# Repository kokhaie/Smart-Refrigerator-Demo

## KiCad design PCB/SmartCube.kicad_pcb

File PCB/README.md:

# PCB Bill of Materials

The KiCad-generated BOM is mirrored into the documentation site under `docs/` so it can be published through GitHub Pages.

- **Live BOM:** https://kokhaie.github.io/Smart-Refrigerator-Demo/bom.html

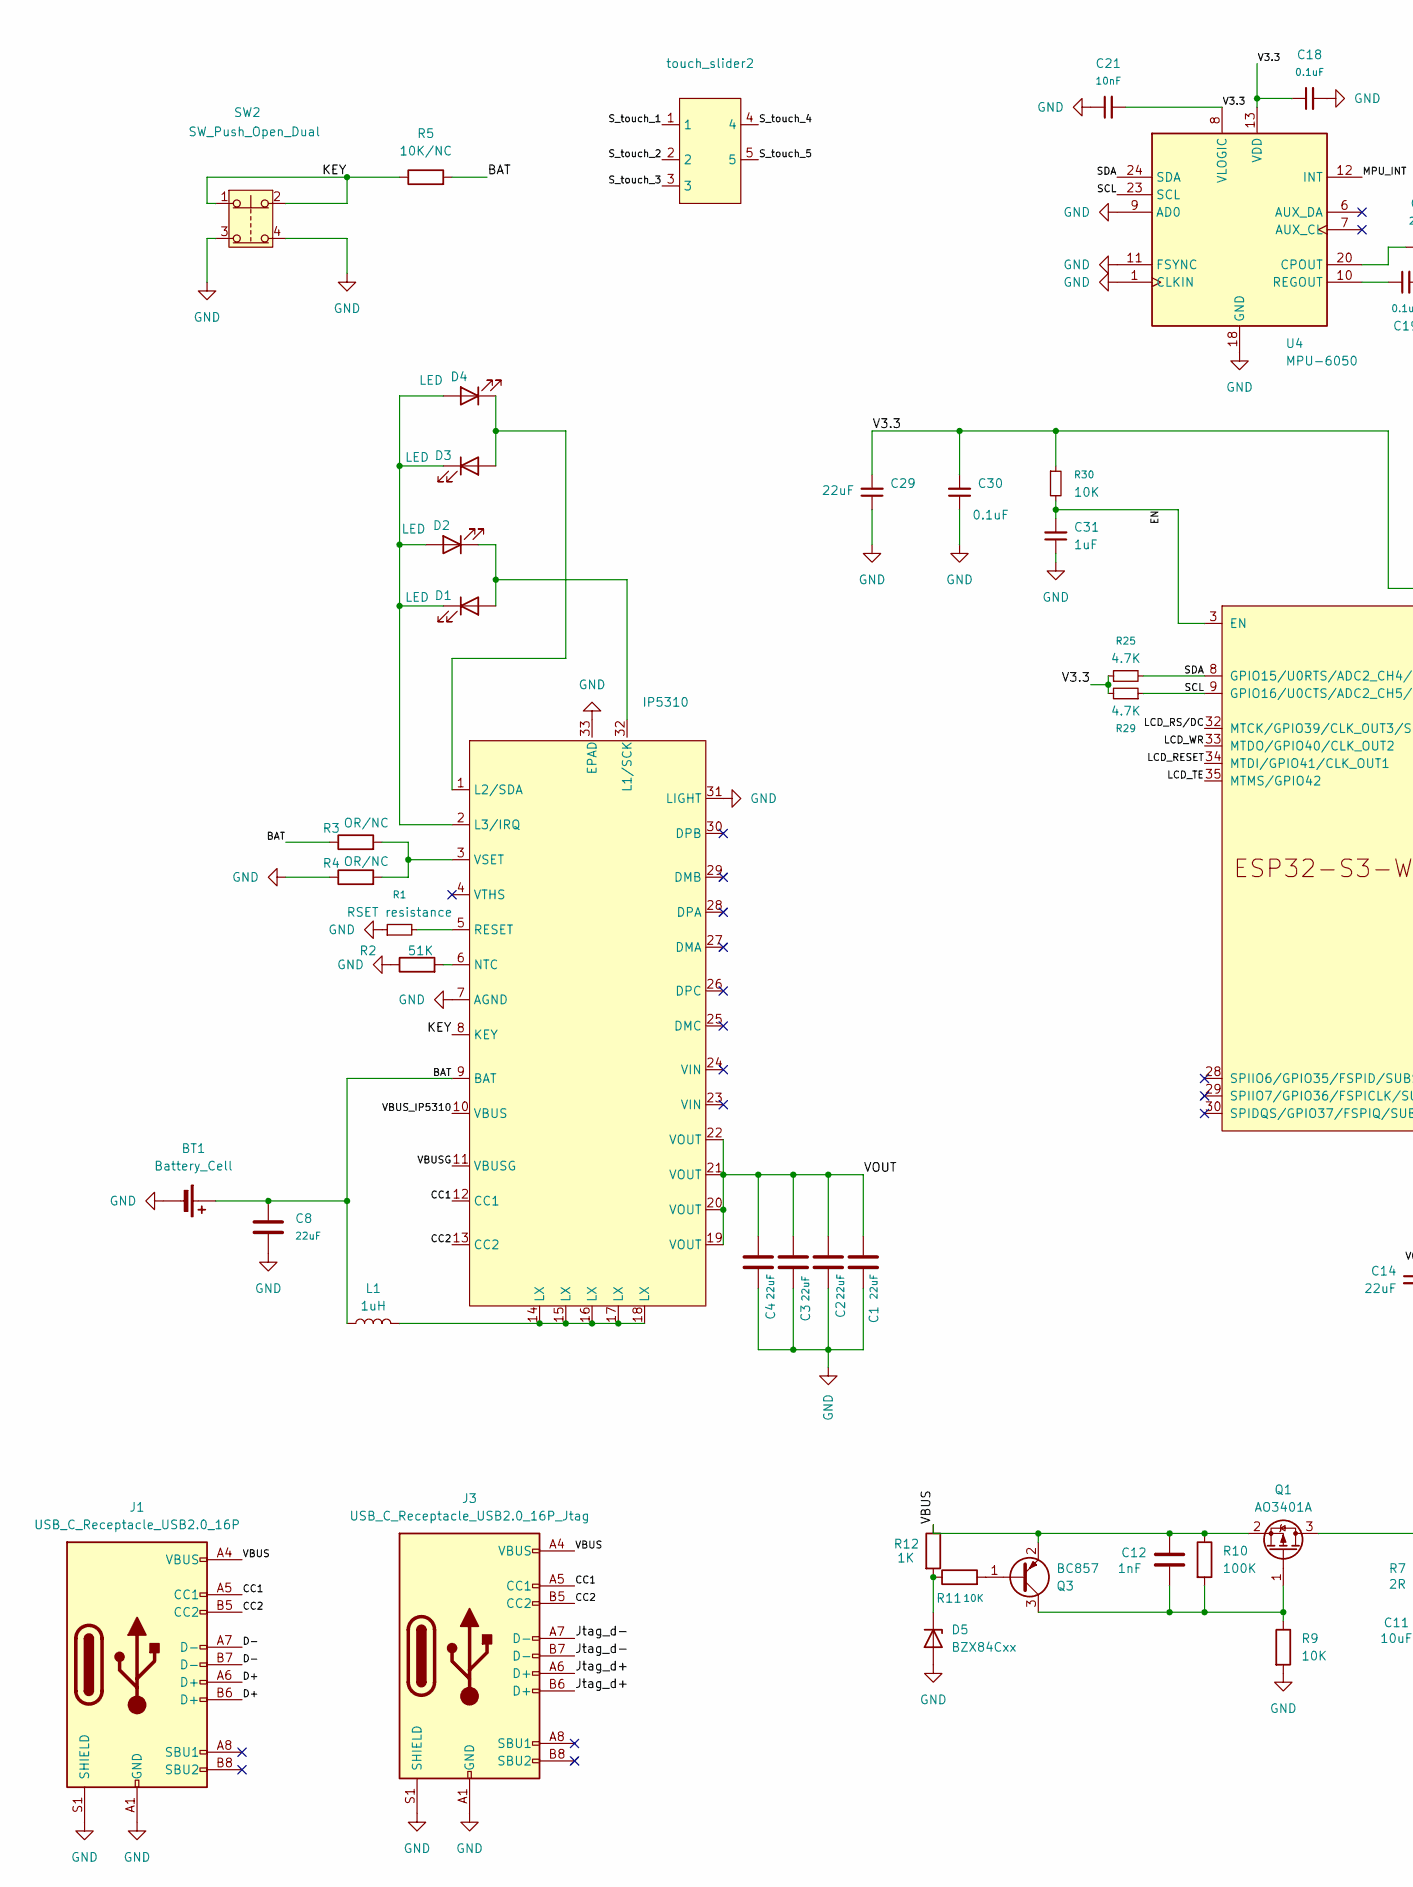
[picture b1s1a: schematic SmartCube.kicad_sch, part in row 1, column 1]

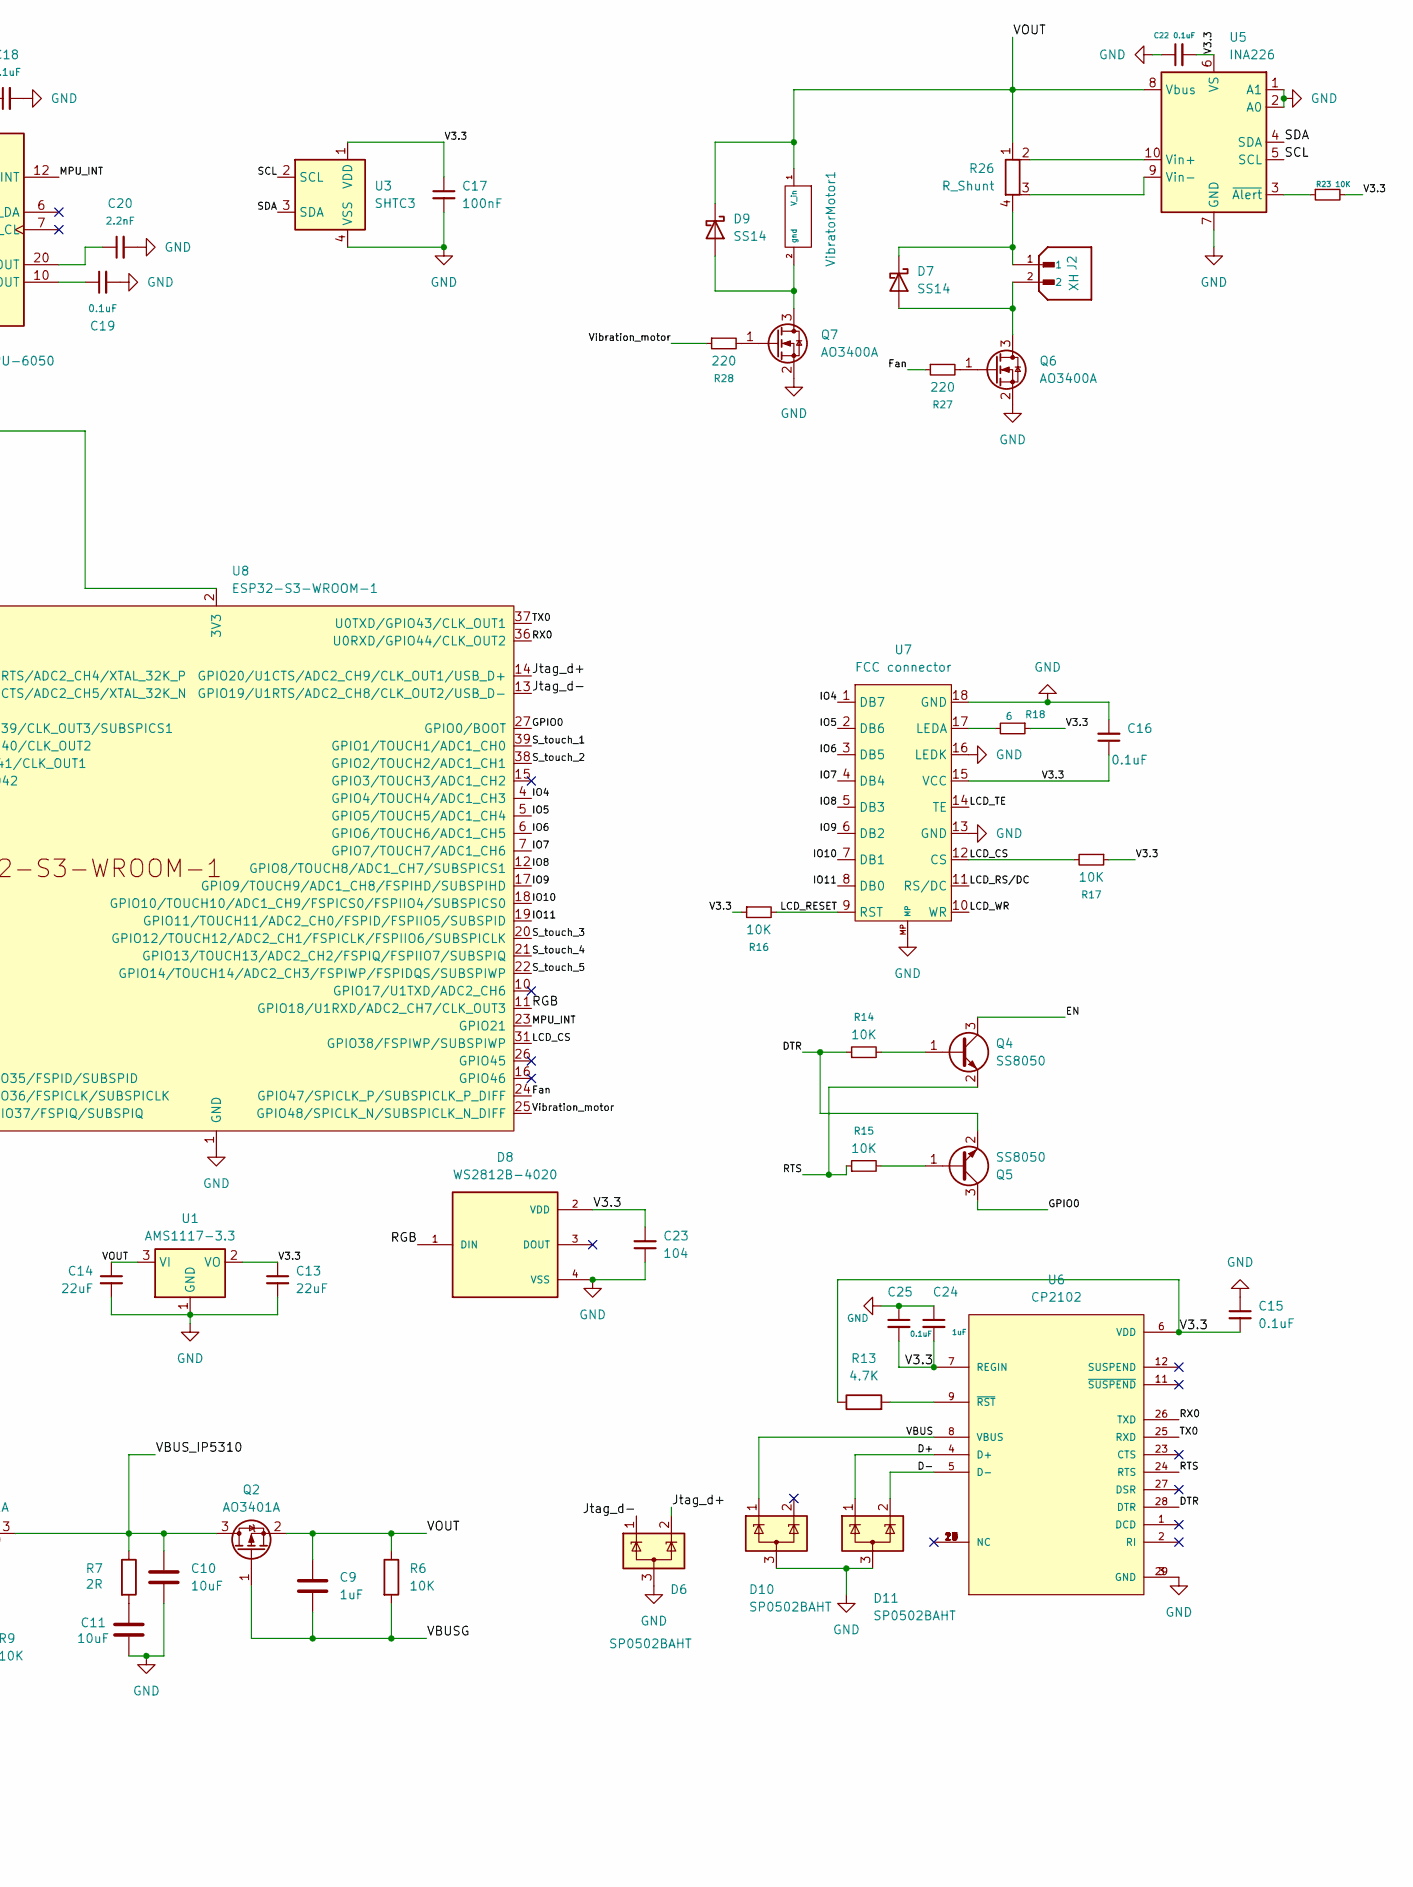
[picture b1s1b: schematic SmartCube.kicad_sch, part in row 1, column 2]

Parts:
BT1: Battery_Cell; vibrator connector
C1, C2, C3, C4, C8, C13, C14: 22uF; C_0805_2012Metric
C9, C24, C31: 1uF; C_0805_2012Metric
C10, C11: 10uF; C_0805_2012Metric
C12: 1nF; C_0805_2012Metric
C15, C16, C18, C19, C22, C25, C30: 0.1uF; C_0805_2012Metric
C17: 100nF; C_0805_2012Metric
C20: 2.2nF; C_0805_2012Metric
C21: 10nF; C_0805_2012Metric
C23: 104; C_0805_2012Metric
C29: 22uF; CP_EIA-3528-21_Kemet-B
D1, D2, D3, D4: LED; LED_0603_1608Metric
D5: BZX84Cxx; SOT-23
D6, D10, D11: SP0502BAHT; SOT-23
D7, D9: SS14; D_SMA
D8: WS2812B-4020; LED_WS2812B-4020; PARTREV V1.2
IP5310: IP5310
J1: USB_C_Receptacle_USB2.0_16P; USB_C_Receptacle_GCT_USB4105-xx-A_16P_TopMnt_Horizontal
J2: XH; vibrator connector; PARTREV N/A
J3: USB_C_Receptacle_USB2.0_16P_Jtag; USB_C_Receptacle_GCT_USB4105-xx-A_16P_TopMnt_Horizontal
L1: 1uH; L_7.3x7.3_H4.5
Q1, Q2: AO3401A; SOT-23
Q3: BC857; SOT-23
Q4, Q5: SS8050; SOT-23
Q6, Q7: AO3400A; SOT-23
R1: RSET resistance; R_0805_2012Metric
R2: 51K; R_0603_1608Metric
R3, R4: OR/NC; R_0805_2012Metric
R5: 10K/NC; R_0805_2012Metric
R6, R9, R11, R14, R15, R16, R17, R23, R30: 10K; R_0805_2012Metric
R7: 2R; R_0805_2012Metric
R10: 100K; R_0805_2012Metric
R12: 1K; R_0805_2012Metric
R13, R25, R29: 4.7K; R_0805_2012Metric
R18: 6; R_0805_2012Metric
R26: R_Shunt; R_Shunt_Vishay_WSK2512_6332Metric_T1.19mm
R27, R28: 220; R_0805_2012Metric
SW2: SW_Push_Open_Dual; 1189UE
U1: AMS1117-3.3; SOT-223-3_TabPin2
U3: SHTC3; Sensirion_DFN-4-1EP_2x2mm_P1mm_EP0.7x1.6mm
U4: MPU-6050; InvenSense_QFN-24_4x4mm_P0.5mm
U5: INA226; VSSOP-10_3x3mm_P0.5mm
U6: CP2102; QFN50P500X500X100-29N
U7: FCC connector; Untitled
U8: ESP32-S3-WROOM-1
VibratorMotor1: vibrator connector
touch_slider2: TouchSlider-5_50x10mm

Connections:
/BAT: BT1.1 (+), C8.1, IP5310.9 (BAT), L1.1, R3.1, R5.2
/CC1: IP5310.12 (CC1), J1.A5 (CC1), J3.A5 (CC1)
/CC2: IP5310.13 (CC2), J1.B5 (CC2), J3.B5 (CC2)
/D+: D11.1 (K), J1.A6 (D+), J1.B6 (D+), U6.4 (D+)
/D-: D11.2 (K), J1.A7 (D-), J1.B7 (D-), U6.5 (D-)
/DTR: Q5.2 (E), R14.1, U6.28 (DTR)
/EN: C31.2, Q4.3 (C), R30.2, U8.3 (EN)
/Fan: R27.1, U8.24 (GPIO47/SPICLK_P/SUBSPICLK_P_DIFF)
/GPIO0: Q5.3 (C), U8.27 (GPIO0/BOOT)
/IO4: U7.1 (DB7), U8.4 (GPIO4/TOUCH4/ADC1_CH3)
/IO5: U7.2 (DB6), U8.5 (GPIO5/TOUCH5/ADC1_CH4)
/IO6: U7.3 (DB5), U8.6 (GPIO6/TOUCH6/ADC1_CH5)
/IO7: U7.4 (DB4), U8.7 (GPIO7/TOUCH7/ADC1_CH6)
/IO8: U7.5 (DB3), U8.12 (GPIO8/TOUCH8/ADC1_CH7/SUBSPICS1)
/IO9: U7.6 (DB2), U8.17 (GPIO9/TOUCH9/ADC1_CH8/FSPIHD/SUBSPIHD)
/IO10: U7.7 (DB1), U8.18 (GPIO10/TOUCH10/ADC1_CH9/FSPICS0/FSPIIO4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)
/IO11: U7.8 (DB0), U8.19 (GPIO11/TOUCH11/ADC2_CH0/FSPID/FSPIIO5/S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)
/Jtag_d+: D6.2 (K), J3.A6 (D+), J3.B6 (D+), U8.14 (GPIO20/U1CTS/ADC2_CH9/CLK_OUT1/USB_D+)
/Jtag_d-: D6.1 (K), J3.A7 (D-), J3.B7 (D-), U8.13 (GPIO19/U1RTS/ADC2_CH8/CLK_OUT2/USB_D-)
/KEY: IP5310.8 (KEY), R5.1, SW2.1, SW2.2
/LCD_CS: R17.2, U7.12 (CS), U8.31 (GPIO38/FSPIWP/SUBSPIWP)
/LCD_RESET: R16.2, U7.9 (RST), U8.34 (MTDI/GPIO41/CLK_OUT1)
/LCD_RS/DC: U7.11 (RS/DC), U8.32 (MTCK/GPIO39/CLK_OUT3/SUBSPICS1)
/LCD_TE: U7.14 (TE), U8.35 (MTMS/GPIO42)
/LCD_WR: U7.10 (WR), U8.33 (MTDO/GPIO40/CLK_OUT2)
/MPU_INT: U4.12 (INT), U8.23 (GPIO21)
/RGB: D8.1 (DIN), U8.11 (GPIO18/U1RXD/ADC2_CH7/CLK_OUT3); also elsewhere on the board
/RTS: Q4.2 (E), R15.1, U6.24 (RTS)
/RX0: U6.26 (TXD), U8.36 (U0RXD/GPIO44/CLK_OUT2)
/SCL: R29.1, U3.2 (SCL), U4.23 (SCL), U5.5 (SCL), U8.9 (GPIO16/U0CTS/ADC2_CH5/XTAL_32K_N)
/SDA: R25.2, U3.3 (SDA), U4.24 (SDA), U5.4 (SDA), U8.8 (GPIO15/U0RTS/ADC2_CH4/XTAL_32K_P)
/S_touch_1: U8.39 (GPIO1/TOUCH1/ADC1_CH0), touch_slider2.1
/S_touch_2: U8.38 (GPIO2/TOUCH2/ADC1_CH1), touch_slider2.2
/S_touch_3: U8.20 (GPIO12/TOUCH12/ADC2_CH1/FSPICLK/FSPIIO6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), touch_slider2.3
/S_touch_4: U8.21 (GPIO13/TOUCH13/ADC2_CH2/FSPIQ/FSPIIO7/S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), touch_slider2.4
/S_touch_5: U8.22 (GPIO14/TOUCH14/ADC2_CH3/FSPIWP/FSPIDQS/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), touch_slider2.5
/TX0: U6.25 (RXD), U8.37 (U0TXD/GPIO43/CLK_OUT1)
/V3.3: C13.1, C15.2, C16.1, C17.1, C18.1, C21.2, C22.2, C23.2, C24.2, C25.2, C29.2, C30.2, D8.2 (VDD), R13.1, R16.1, R17.1, R18.1, R23.2, R25.1, R29.2, R30.1, U1.2 (VO), U3.1 (VDD), U4.8 (VLOGIC), U4.13 (VDD), U5.6 (VS), U6.6 (VDD), U6.7 (REGIN), U7.15 (VCC), U8.2 (3V3); also elsewhere on the board
/VBUS: C12.1, D10.1 (K), J1.A4 (VBUS), J1.A9 (VBUS), J1.B4 (VBUS), J1.B9 (VBUS), J3.A4 (VBUS), J3.A9 (VBUS), J3.B4 (VBUS), J3.B9 (VBUS), Q1.2 (S), Q3.2 (E), R10.1, R12.1, U6.8 (VBUS)
/VBUSG: C9.2, IP5310.11 (VBUSG), Q2.1 (G), R6.2
/VBUS_IP5310: C10.1, IP5310.10 (VBUS), Q1.3 (D), Q2.3 (D), R7.1
/VOUT: C1.1, C2.1, C3.1, C4.1, C9.1, C14.1, D9.1 (K), IP5310.19 (VOUT), IP5310.20 (VOUT), IP5310.21 (VOUT), IP5310.22 (VOUT), Q2.2 (S), R6.1, R26.1, U1.3 (VI), U5.8 (Vbus), VibratorMotor1.1 (V_in)
/Vibration_motor: R28.1, U8.25 (GPIO48/SPICLK_N/SUBSPICLK_N_DIFF)
GND: BT1.2 (-), C1.2, C2.2, C3.2, C4.2, C8.2, C10.2, C11.2, C13.2, C14.2, C15.1, C16.2, C17.2, C18.2, C19.2, C20.2, C21.1, C22.1, C23.1, C24.1, C25.1, C29.1, C30.1, C31.1, D5.1 (A), D6.3 (A), D8.4 (VSS), D10.3 (A), D11.3 (A), IP5310.7 (AGND), IP5310.31 (LIGHT), IP5310.33 (EPAD), J1.A1 (GND), J1.A12 (GND), J1.B1 (GND), J1.B12 (GND), J1.S1 (SHIELD), J3.A1 (GND), J3.A12 (GND), J3.B1 (GND), J3.B12 (GND), J3.S1 (SHIELD), Q6.2 (S), Q7.2 (S), R1.1, R2.1, R4.1, R9.2, SW2.3, SW2.4, U1.1 (GND), U3.4 (VSS), U4.1 (CLKIN), U4.9 (AD0), U4.11 (FSYNC), U4.18 (GND), U5.1 (A1), U5.2 (A0), U5.7 (GND), U6.3 (GND), U6.29 (GND), U7.13 (GND), U7.16 (LEDK), U7.18 (GND), U7.MP, U8.1 (GND), U8.40 (GND), U8.41 (GND); also elsewhere on the board
unnamed: C11.1, R7.2
unnamed: D1.2 (A), D2.1 (K), IP5310.32 (L1/SCK)
unnamed: D1.1 (K), D2.2 (A), D3.1 (K), D4.2 (A), IP5310.2 (L3/IRQ)
unnamed: D3.2 (A), D4.1 (K), IP5310.1 (L2/SDA)
unnamed: D5.3 (K), R11.1, R12.2
unnamed: D7.2 (A), J2.2, Q6.3 (D)
unnamed: D7.1 (K), J2.1, R26.4
unnamed: D9.2 (A), Q7.3 (D), VibratorMotor1.2 (gnd)
unnamed: IP5310.14 (LX), IP5310.15 (LX), IP5310.16 (LX), IP5310.17 (LX), IP5310.18 (LX), L1.2
unnamed: IP5310.6 (NTC), R2.2
unnamed: IP5310.5 (RESET), R1.2
unnamed: IP5310.3 (VSET), R3.2, R4.2
unnamed: C12.2, Q1.1 (G), Q3.3 (C), R9.1, R10.2
unnamed: Q3.1 (B), R11.2
unnamed: Q4.1 (B), R14.2
unnamed: Q5.1 (B), R15.2
unnamed: Q6.1 (G), R27.2
unnamed: Q7.1 (G), R28.2
unnamed: C20.1, U4.20 (CPOUT)
unnamed: C19.1, U4.10 (REGOUT)
unnamed: R26.2, U5.10 (Vin+)
unnamed: R26.3, U5.9 (Vin-)
unnamed: R23.1, U5.3 (~Alert)
unnamed: R13.2, U6.9 (~RST)
unnamed: R18.2, U7.17 (LEDA)

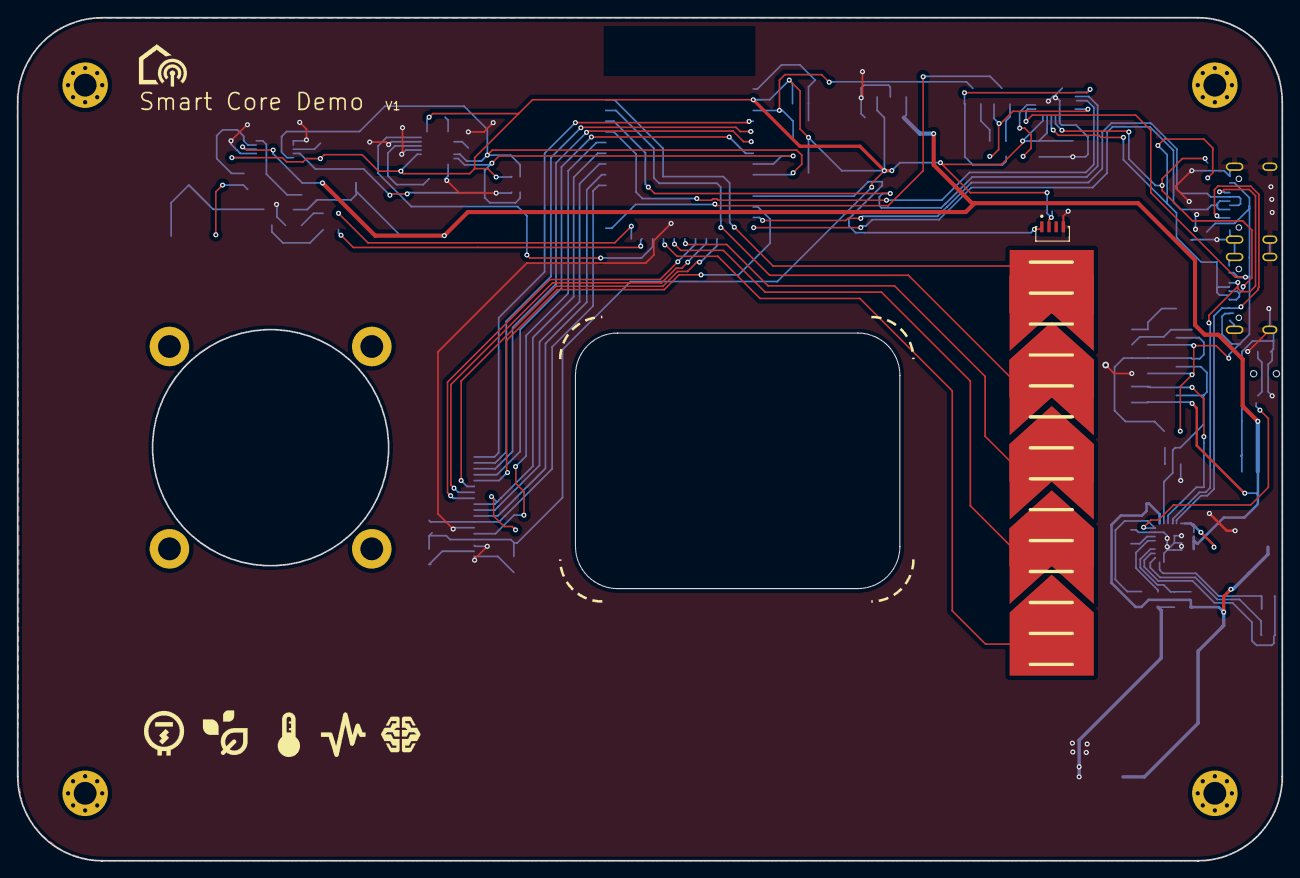
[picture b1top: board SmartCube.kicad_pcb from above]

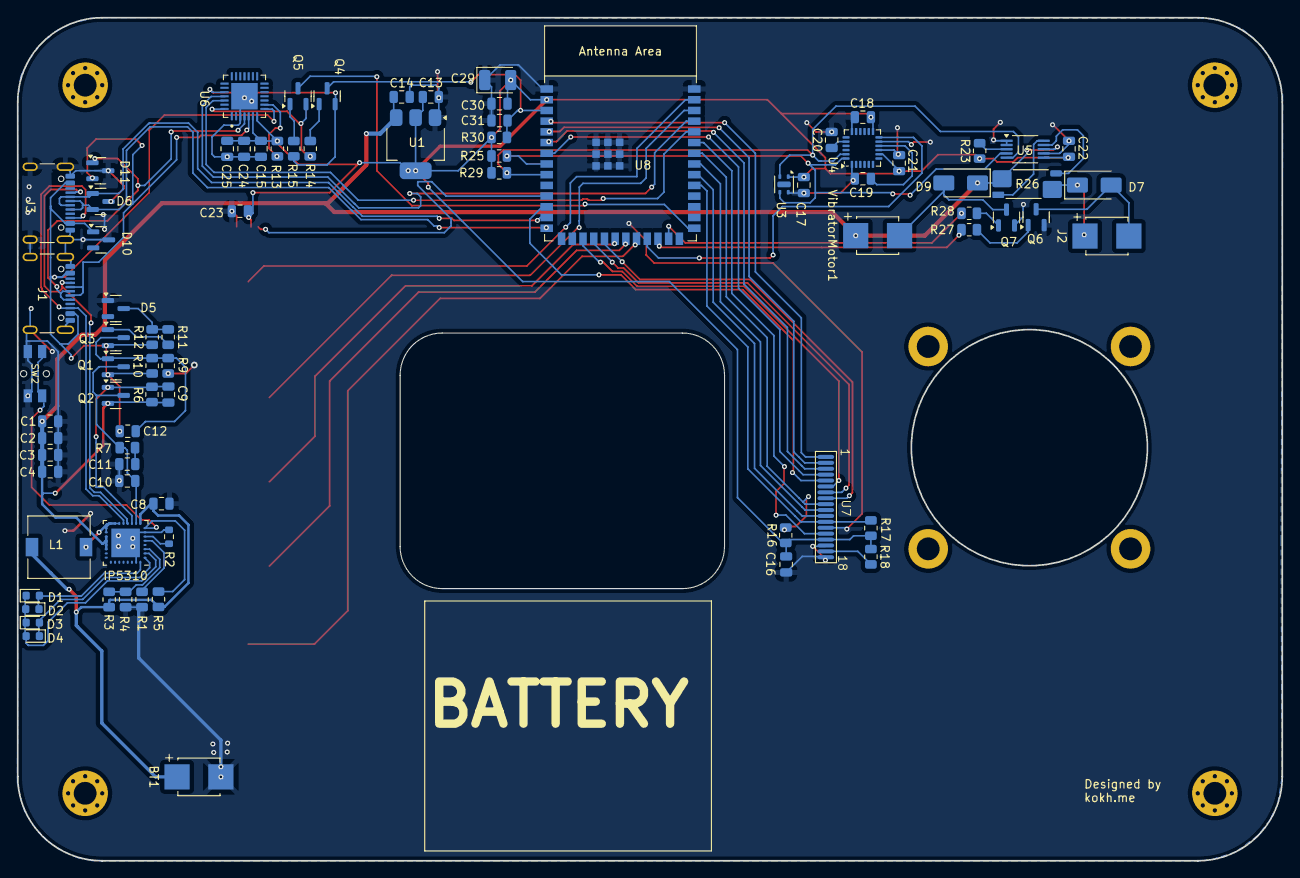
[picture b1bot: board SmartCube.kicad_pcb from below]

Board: 2 copper layers, 150.0 x 100.0 mm, 83 parts (81 on the bottom side), 69 nets.

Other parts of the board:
RGB: WS2812B-4020; LED_WS2812B-4020

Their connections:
/RGB: RGB.1 (DIN); also elsewhere on the board
/V3.3: RGB.2 (VDD); also elsewhere on the board
GND: RGB.4 (VSS); also elsewhere on the board

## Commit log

2025-09-05 First Schema Version
2025-09-05 Update Schema and add SP0502BAHAT
2025-09-06 Add footprints to schema
2025-09-07 Add first version of pcb
2025-09-08 Initialize first pcb version
2025-09-15 Add jtag USB
2025-09-15 Remove build folder
2025-09-20 Add motors component
2025-09-23 Add freeRTOS tasks for each component
2025-09-23 Add data publiser for mqtt message
2025-09-23 feat(network): add mqtt broker and implement non blocking wifi connection
2025-09-25 feat(network): Add local broker and wifi management
2025-09-25 docs: Add datasheets
2025-09-25 fix(ui): Update lcd driver
2025-09-26 feat(ui): Add first main screen
2025-09-26 feat(ui): Add lottie animation
2025-10-03 Comment out sensor init
2025-10-03 add sensor Kconfig
2025-10-04 feat(sensor): Add fifo(mpu6050)
2025-10-04 fix(sensor): add delay end of the loop of reading sensors
2025-10-06 fix(ui): Fix i80 controller driver misconfig
2025-10-11 fix(sensor): Pack the sensor data
2025-10-12 feat(sensor_manager): add sensor acquisition and synchronization - Support MPU6050 (FIFO + interrupt-driven reads), INA226, and SHTC3 - Protect shared state with mutexes - Provide stream queue (drop-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
2025-10-12 feat(data_publisher): implement MQTT publishing for sensors - Publish real-time stream at 10Hz (device/realtime/samples) - Publish batch data as JSON arrays (device/training/samples) - Add slider set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
2025-10-12 feat(network_manager): support remote broker and fallback AP mode - Wi-Fi STA connects to remote broker with retries + timeout - On failure, switch to AP mode and run embedded MQTT broker - Introduce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
2025-10-12 refactor(main): wire up sensor manager, publisher, and business logic - Start all core components in app_main - Run tasks pinned to appropriate cores for performance
2025-10-13 feat(business_logic): add deadband and integral decay for stable fan control
    ### Why
    - The fan was staying at a low duty cycle (e.g. ~10%) indefinitely once the system
    reached the setpoint, due to integral windup.
    - Small temperature fluctuations caused unnecessary fan activity.
    ### What
    - Introduced a ±0.5 °C deadband around the setpoint to ignore tiny fluctuations.
2025-10-14 fit(ui_manager):Add lcd color test
2025-10-14 feat: add LED manager component with basic UI modes and startup animation
    - Created new led_manager component to handle WS2812B LED control
    - Implemented LED modes:
    • NORMAL mode → shows setpoint as solid color mapped to temperature range
    • ECO mode → green indicator
    • SUPERCOOL mode → blue indicator
    • ERROR mode → red indicator
2025-10-15 Add UI controller and refine slider UX
2025-10-16 fix(ui_controller):Update bussiness logic setpoint temp using touch slider
2025-10-16 Add plexi enclosure box design
2025-10-16 refactor(components):Rename components
2025-10-17 Initail working lottie animation
2025-10-17 fix(lottie): Add psram
2025-10-17 fix(lcd_manager):Rotate screen 270 degree
2025-10-21 feat(ui): reorganize lcd manager and add smart/eco/rapid modes
    - restructure lcd_manager into src/ui/assets and fix CMake paths
    - add Smart/Eco/Rapid mode profiles across business logic and UI
    - update LCD badge defaults and generated assets to match new layout
    - widen slider margins so touch gestures don’t pin the physical edges
2025-10-28 feat(anomally_detection): Add infrence
2025-10-28 Add Jupeter Notebook
2025-10-28 Update .gitignore
    Add python venv folder
2025-10-28 Reorganize Anomaly detector's structure
2025-10-28 Add PCB BOM
2025-10-28 Update Docs
2025-10-28 Initialize flutter app
